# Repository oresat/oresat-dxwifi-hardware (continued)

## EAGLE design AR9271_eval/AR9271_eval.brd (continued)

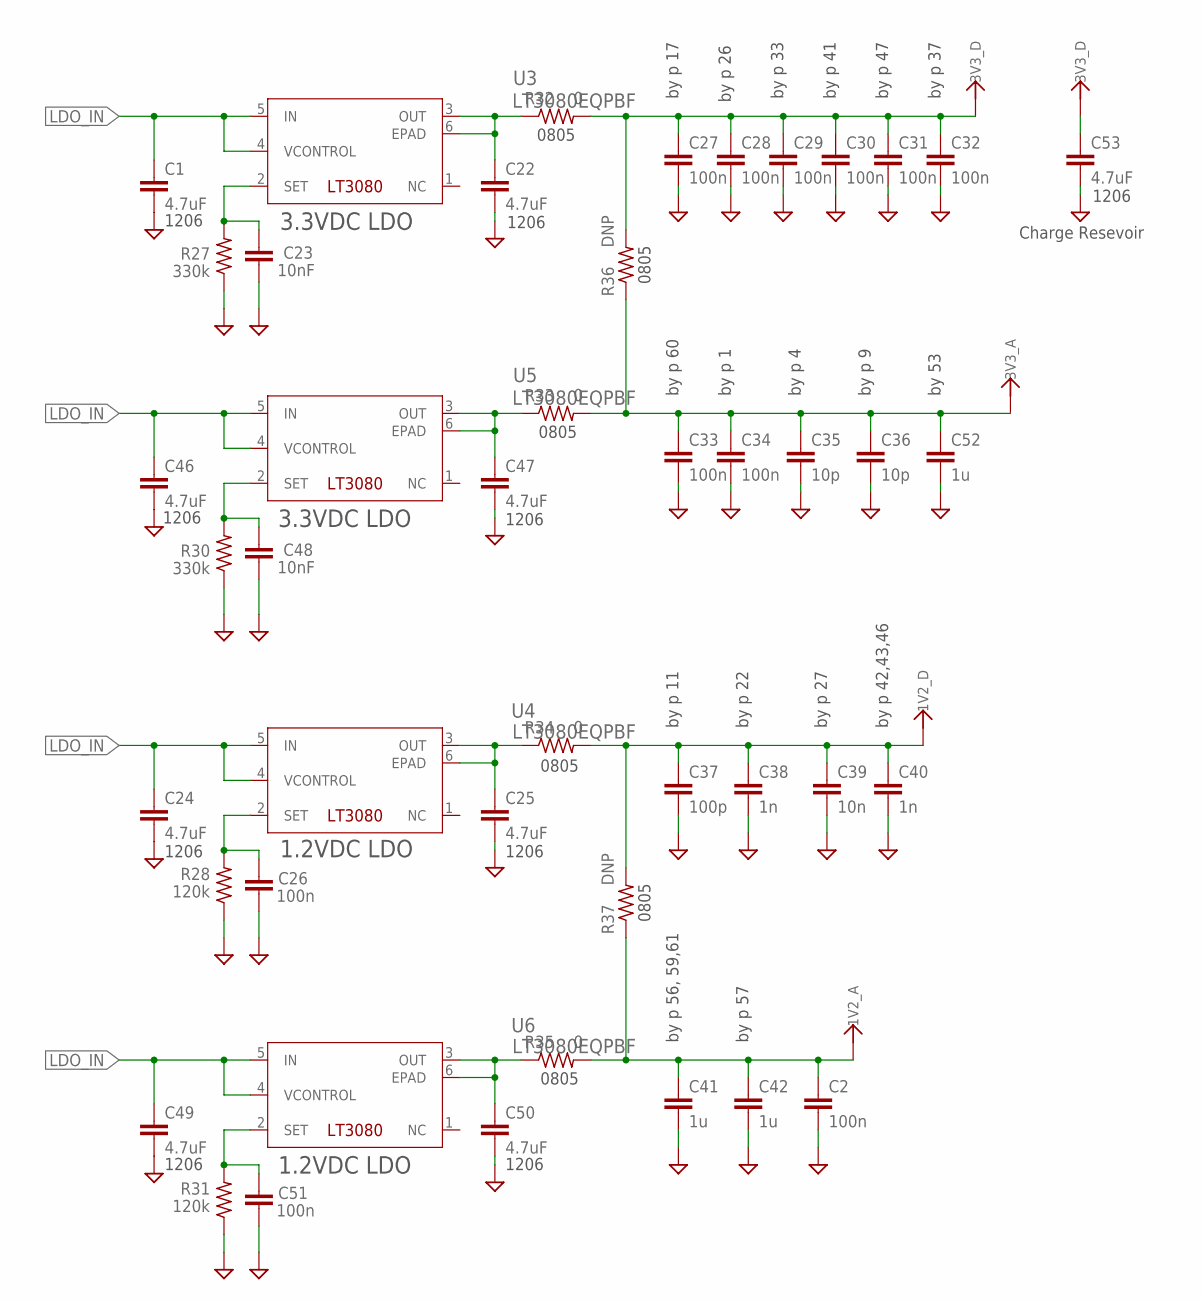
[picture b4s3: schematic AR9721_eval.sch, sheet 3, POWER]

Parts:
C1, C22, C24, C25, C46, C47, C49, C50, C53: 4.7uF; C1206; MPN GCM31CR71C475KA37L
C2: 100n; .0402-B-NOSILK; MPN GRM155R70J105KA12J
C23, C48: 10nF; .0402-B-NOSILK; MPN C0402C103K4RACAUTO
C26, C27, C28, C29, C30, C31, C32, C33, C34, C51: 100n; .0402-B-NOSILK; MPN CGA2B1X7R1C104K050BC
C35, C36: 10p; .0402-B-NOSILK; MPN CGA2B2C0G1H100D050BA
C37: 100p; .0402-B-NOSILK; MPN CGA2B2C0G1H101J050BA
C38, C40: 1n; .0402-B-NOSILK; MPN C0402C102K5GACTU
C39: 10n; .0402-B-NOSILK; MPN C0402C103K4RACAUTO
C41, C42: 1u; .0402-B-NOSILK; MPN GRM155R70J105KA12J
C52: 1u; .0402-B-NOSILK; MPN CGA2B2C0G1H100D050BA
R27, R30: 330k; .0402-A-NOSILK; MPN ERJ-2RKF3303X
R28, R31: 120k; .0402-A-NOSILK; MPN ERJ-2RKF1203X
R32, R33, R34, R35: 0; .0805-B; MPN ERJ-6GEY0R00V
R36, R37: DNP; .0805-B; MPN ERJ-6GEY0R00V
U3, U4, U5, U6: LT3080EQPBF; DDPAK-5_Q

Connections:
1V2_A: C2.1, C41.1, C42.1, R35.2, R37.1; also elsewhere on the board
1V2_D: C37.1, C38.1, C39.1, C40.1, R34.2, R37.2; also elsewhere on the board
3V3_A: C33.1, C34.1, C35.1, C36.1, C52.1, R33.2, R36.1; also elsewhere on the board
3V3_D: C27.1, C28.1, C29.1, C30.1, C31.1, C32.1, C53.1, R32.2, R36.2; also elsewhere on the board
GND: C1.2, C2.2, C22.2, C23.2, C24.2, C25.2, C26.2, C27.2, C28.2, C29.2, C30.2, C31.2, C32.2, C33.2, C34.2, C35.2, C36.2, C37.2, C38.2, C39.2, C40.2, C41.2, C42.2, C46.2, C47.2, C48.2, C49.2, C50.2, C51.2, C52.2, C53.2, R27.1, R28.1, R30.1, R31.1; also elsewhere on the board
LDO_IN: C1.1, C24.1, C46.1, C49.1, U3.4 (VCONTROL), U3.5 (IN), U4.4 (VCONTROL), U4.5 (IN), U5.4 (VCONTROL), U5.5 (IN), U6.4 (VCONTROL), U6.5 (IN); also elsewhere on the board
unnamed: C23.1, R27.2, U3.2 (SET)
unnamed: C26.1, R28.2, U4.2 (SET)
unnamed: C22.1, R32.1, U3.3 (OUT), U3.6 (EPAD)
unnamed: C25.1, R34.1, U4.3 (OUT), U4.6 (EPAD)
unnamed: C48.1, R30.2, U5.2 (SET)
unnamed: C47.1, R33.1, U5.3 (OUT), U5.6 (EPAD)
unnamed: C51.1, R31.2, U6.2 (SET)
unnamed: C50.1, R35.1, U6.3 (OUT), U6.6 (EPAD)

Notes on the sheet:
0805
3.3VDC LDO
1.2VDC LDO
1206
by p 60
by p 1
by p 4
by p 9
by p 17
by p 26
by p 33
by p 41
by p 47
by p 37
by p 11
by p 22
by p 27
by p 42,43,46
by p 56, 59,61
by p 57
by 53
Charge Resevoir

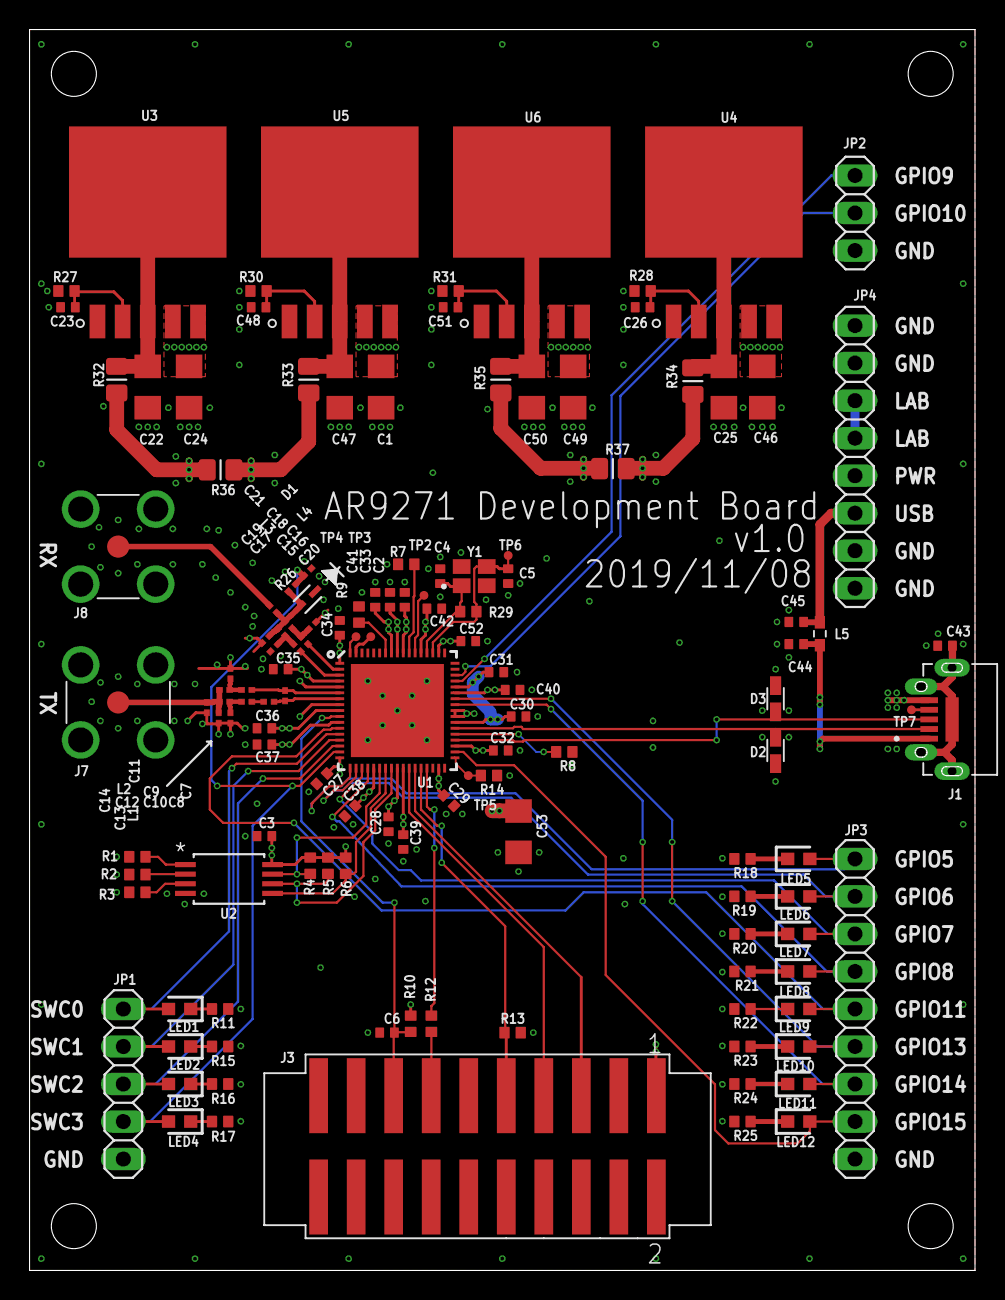
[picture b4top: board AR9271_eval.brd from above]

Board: 4 copper layers, 64.0 x 84.0 mm, 135 parts (0 on the bottom side), 80 nets.

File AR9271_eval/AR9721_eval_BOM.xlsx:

Bill Of Materials for AR9721
Source file: AR9721_eval.sch
Last modified: 2019/09/17
PCB version: 1.0 |  |  | P/DNP = | Place/Do Not Place (DNP is for final production boards)
BOM revision: 0 |  |  | Generic = | Any generic part with the same characteristics are OK (e.g., bypass cap)
Cnt | Part References | P/DNP | Mfg | Mfg PN | Description | Generic | Dist | Dist Part Number
9 | C1, C22, C24, C25, C46, C47, C49, C50, C53 | P | Murata Electronics | GCM31CR71C475KA37L | Capacitor, 4.7uF, 1206 | Y | Digi-key | 490-6065-1-ND
4 | C10, C11, C12, C13 | P | Taiyo Yuden | UMK063CG020CTHF | Capacitor, 2pF, 0201 | Y | Digi-key | 587-3777-2-ND
2 | C14, C19 | P | Taiyo Yuden | UMK063CG010CTHF | Capacitor, 1pF, 0201 | Y | Digi-key | 587-3776-1-ND
2 | C17, C18 | P | Taiyo Yuden | UMK063CG1R5CT-F | Capacitor, 1.5pF, 0201 | Y | Digi-key | 587-3202-6-ND
15 | C2, C3, C6, C26, C27, C28, C29, C30, C31, C32, C33, C34, C43, C45, C51 | P | TDK | CGA2B1X7R1C104K050BC | Capacitor, 100nF, 0402 | Y | Digi-key | 445-5613-1-ND
1 | C21 | P | Taiyo Yuden | UMK063CG101JT-F | Capacitor, 100pF, 0201 | Y | Digi-key | 587-3207-2-ND
4 | C23, C39, C44, C48 | P | Kemet | C0402C103K4RACAUTO | Capacitor, 10nF, 0402 | Y | Digi-key | 399-6825-1-ND
1 | C37 | P | TDK | CGA2B2C0G1H101J050BA | Capacitor, 100pF, 0402 | Y | Digi-key | 445-5596-1-ND
2 | C38, C40 | P | Kemet | C0402C102K5GACTU | Capacitor, 1nF, 0402 | Y | Digi-key | 399-7756-1-ND
4 | C4, C5, C35, C36 | P | Yageo | CC0402JRNPO9BN100 | Capacitor, 10pF, 0402 | Y | Digi-key | 311-1014-1-ND
3 | C41, C42, C52 | P | TDK | CGA2B2C0G1H100D050BA | Capacitor, 1uF, 0402 | Y | Digi-key | 445-5584-1-ND
1 | C7 | P | Taiyo Yuden | UMK063CG2R2CTHF | Capacitor, 2.2pF, 0201 | Y | Digi-key | 587-5314-1-ND
5 | C8, C9, C15, C16, C20 | P | Taiyo Yuden | UMK063CG100DTHF | Capacitor, 10pF, 0201 | Y | Digi-key | 587-3785-2-ND
1 | D1 | P | Skyworks | SMP1321-079 | RF PIN Diode | N | Digi-key | 863-1099-1-ND
2 | D2, D3 | P | Littelfuse Inc. | PGB1010603MR | PGB1 Series 15 V 63 Bi-Directional SMT ESD TVS | Y | Digi-key | F2594CT-ND
1 | J1 | P | CUI Inc. | UJ2-MIBH2-4-SMT-TR | Micro B Type 5 Pin Horizontal SMT USB Jack 2.0 | Y | Digi-key | 102-4007-1-ND
1 | J3 | P | Samtec Inc. | HTST-110-01-L-DV-P | Conn Shrouded Header HDR 20 POS 2.54mm Solder ST SMD | Y | Digi-key | SAM15675-ND
2 | J7, J8 | P | Amphenol RF | 132134-15 | Rf Coaxial, Sma, Straight Jack, Pcb | Y | Digi-key | ACX1962-ND
4 | JP1, JP2, JP3, JP4 | P | NA | NA | PIN HEADER | Y | Digi-key | 952-3308-ND
2 | L1, L2 | P | Murata Electronics | LQP03TN1N8B02D | Inductor, 1.8nH, 0201 | Y | Digi-key | 490-6720-1-ND
2 | L3, L4 | P | Murata Electronics | LQP03TN2N2B02D | Inductor, 2.2nH, 0201 | Y | Digi-key | 490-6723-1-ND
1 | L5 | P | Murata Electronics | BLM18PG221SH1D | FERRITE BEAD 220 OHM 0603 1LN | N | Digi-key | 490-7817-1-ND
12 | LED1, LED2, LED3, LED4, LED5, LED6, LED7, LED8, LED9, LED10, LED11, LED12 | P | Lite-On | LTST-C193KGKT-5A | LED,Green,0603, | Y | Digi-key | 160-1828-1-ND
3 | R1, R36, R37 | NP | NA | NA | NA | NA | NA | NA
12 | R11, R15, R16, R17, R18, R19, R20, R21, R22, R23, R24, R25 | P | Panasonic | ERJ-2GEJ511X | Resistor, 510, 0402 | Y | Digi-key | P510JTR-ND
1 | R12 | P | Panasonic | ERJ-2GEJ330X | Resistor, 33, 0402 | Y | Digi-key | P33JCT-ND
2 | R2, R3 | P | Panasonic | ERJ-2GE0R00X | Resistor, 0, 0402 | Y | Digi-key | P0.0JCT-ND
1 | R26 | P | Panasonic | ERJ-1GNF1001C | Resistor, 1k, 0201 | Y | Digi-key | P122413CT-ND
2 | R27, R30 | P | Panasonic | ERJ-2RKF3303X | Resistor, 330k, 0402 | Y | Digi-key | P330KLCT-ND
2 | R28, R31 | P | Panasonic | ERJ-2RKF1203X | Resistor, 120k, 0402 | Y | Digi-key | P120KLCT-ND
1 | R29 | P | Panasonic | ERJ-2GEJ105X | Resistor, 1M, 0402 | Y | Digi-key | P1.0MJTR-ND
4 | R32, R33, R34, R35 | P | Panasonic | ERJ-6GEY0R00V | Resistor, 0, 0805 | Y | Digi-key | P0.0ACT-ND
5 | R4, R7, R10, R13, R14 | P | Panasonic | ERJ-2GEJ103X | Resistor, 10k, 0402 | Y | Digi-key | ERJ-2GEJ103X
2 | R5, R6 | P | Panasonic | ERJ-2GEJ103X | Resistor, 4.7k, 0402 | Y | Digi-key | P10KJCT-ND
1 | R8 | P | Panasonic | ERJ-2RKF51R1X | Resistor, 51.1, 0402 | Y | Digi-key | P51.1LCT-ND
1 | R9 | P | Panasonic | ERJ-2RKF6191X | Resistor, 6.19k, 0402 | Y | Digi-key | P6.19KLCT-ND
1 | U1 | P | Atheros | AR9271-AL1A | Atheros WiFi WLAN IC | N | AliExpress | N/A
1 | U2 | P | Microchip | AT24C04CXHMT | EEPROM with I2C interface | N | Digi-key | AT24C04C-XHM-TCT-ND
4 | U3, U4, U5, U6 | P | Analog Devices | LT3080EQ#PBF | Adj. 1.1A Single Res LDO Regulator | N | Digi-key | LT3080EQ#PBF-ND
1 | Y1 | P | ECS International | ECS-400-10-36-CKY-TR | Crystal 40mhz 10pf Smd | N | Digi-key | XC2666CT-ND
VERSION INFO
Rev | Date | Notes
1 | 43725 | First rev BOM

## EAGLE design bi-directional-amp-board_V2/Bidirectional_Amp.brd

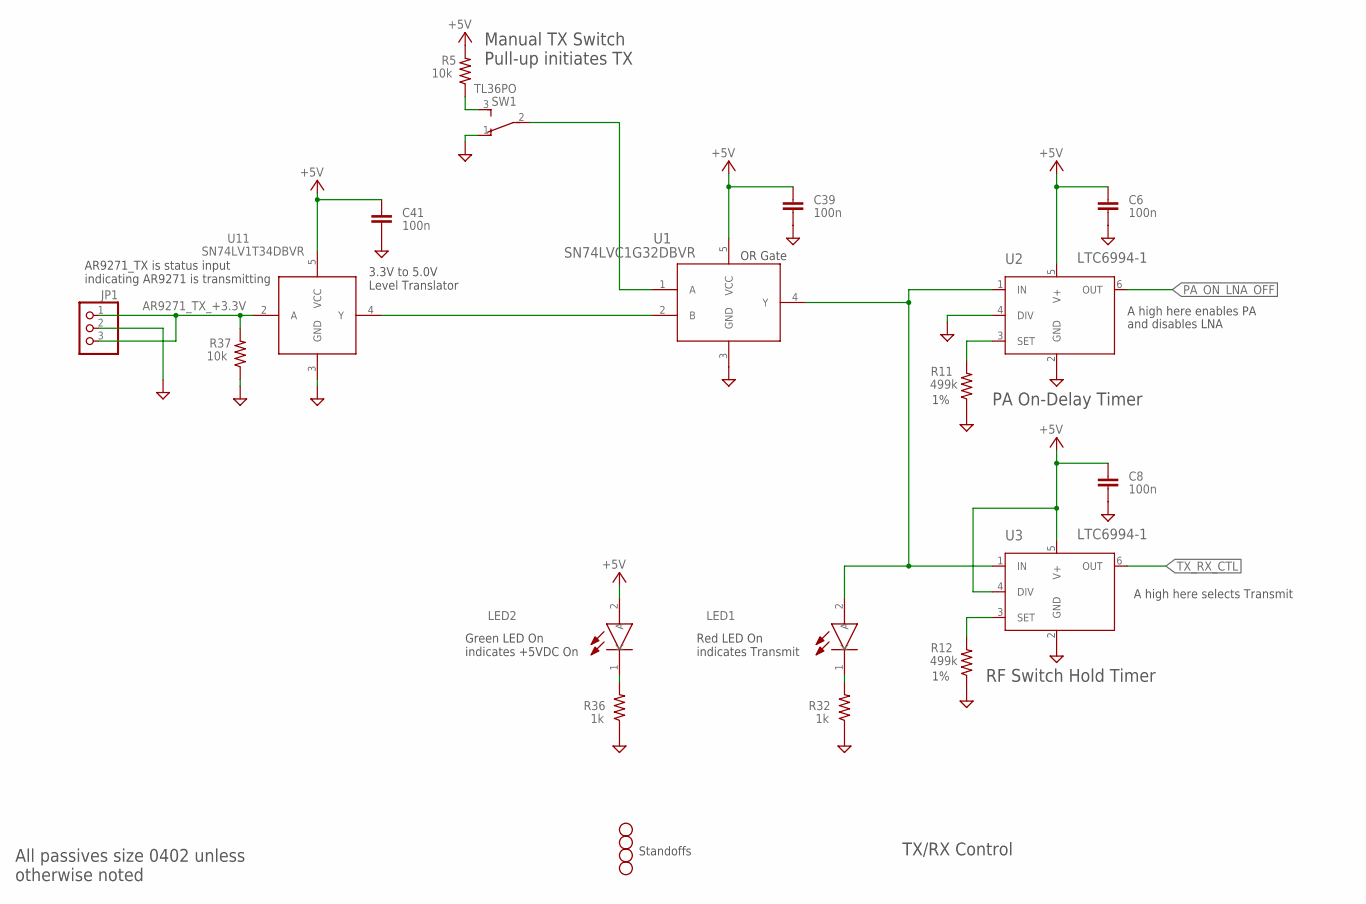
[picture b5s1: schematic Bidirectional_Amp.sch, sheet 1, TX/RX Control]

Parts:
C6, C8, C39, C41: 100n; .0402-B-NOSILK; MPN CGA2B1X7R1C104K050BC
H1, H2, H3, H4: STAND-OFFTIGHT; STAND-OFF-TIGHT
JP1: PINHD-1X3; 1X03; MPN 22-23-2031
LED1: LTST-C193KRKT-5A; LEDC1607X80N
LED2: LTST-C193KGKT-5A; LEDC1607X80N
R5, R37: 10k; .0402-B-NOSILK; MPN ERJ-2GEJ103X
R11, R12: 499k; .0402-B-NOSILK; MPN ERJ-2RKF4993X
R32, R36: 1k; .0402-B-NOSILK; MPN ERJ-2GEJ102X
SW1: TL36PO; TL3XPO; MPN TL36P005000
U1: SN74LVC1G32DBVR; DBV5
U2, U3: LTC6994-1; TSOT-23_S6
U11: SN74LV1T34DBVR; SOT95P280X145-5N

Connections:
+5V: C6.1, C8.1, C39.1, C41.1, LED2.2 (A), R5.2, U1.5 (VCC), U2.5 (V+), U3.4 (DIV), U3.5 (V+), U11.5 (VCC); also elsewhere on the board
AR9271_TX_+3.3V: JP1.1, JP1.3, R37.2, U11.2 (A)
GND: C6.2, C8.2, C39.2, C41.2, JP1.2, R11.1, R12.1, R32.1, R36.1, R37.1, SW1.1 (O), U1.3 (GND), U2.2 (GND), U2.4 (DIV), U3.2 (GND), U11.3 (GND); also elsewhere on the board
unnamed: R5.1, SW1.3 (S)
unnamed: SW1.2, U1.1 (A)
unnamed: LED1.2 (A), U1.4 (Y), U2.1 (IN), U3.1 (IN)
unnamed: R11.2, U2.3 (SET)
unnamed: U1.2 (B), U11.4 (Y)
unnamed: R12.2, U3.3 (SET)
unnamed: LED1.1 (K), R32.2
unnamed: LED2.1 (K), R36.2
PA_ON_LNA_OFF: U2.6 (OUT); also elsewhere on the board
TX_RX_CTL: U3.6 (OUT); also elsewhere on the board

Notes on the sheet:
PA On-Delay Timer
RF Switch Hold Timer
Manual TX Switch Pull-up initiates TX
A high here enables PA
and disables LNA
A high here selects Transmit
AR9271_TX is status input indicating AR9271 is transmitting
TX/RX Control
Red LED On indicates Transmit
Green LED On indicates +5VDC On
OR Gate
3.3V to 5.0V Level Translator
Standoffs
All passives size 0402 unless otherwise noted

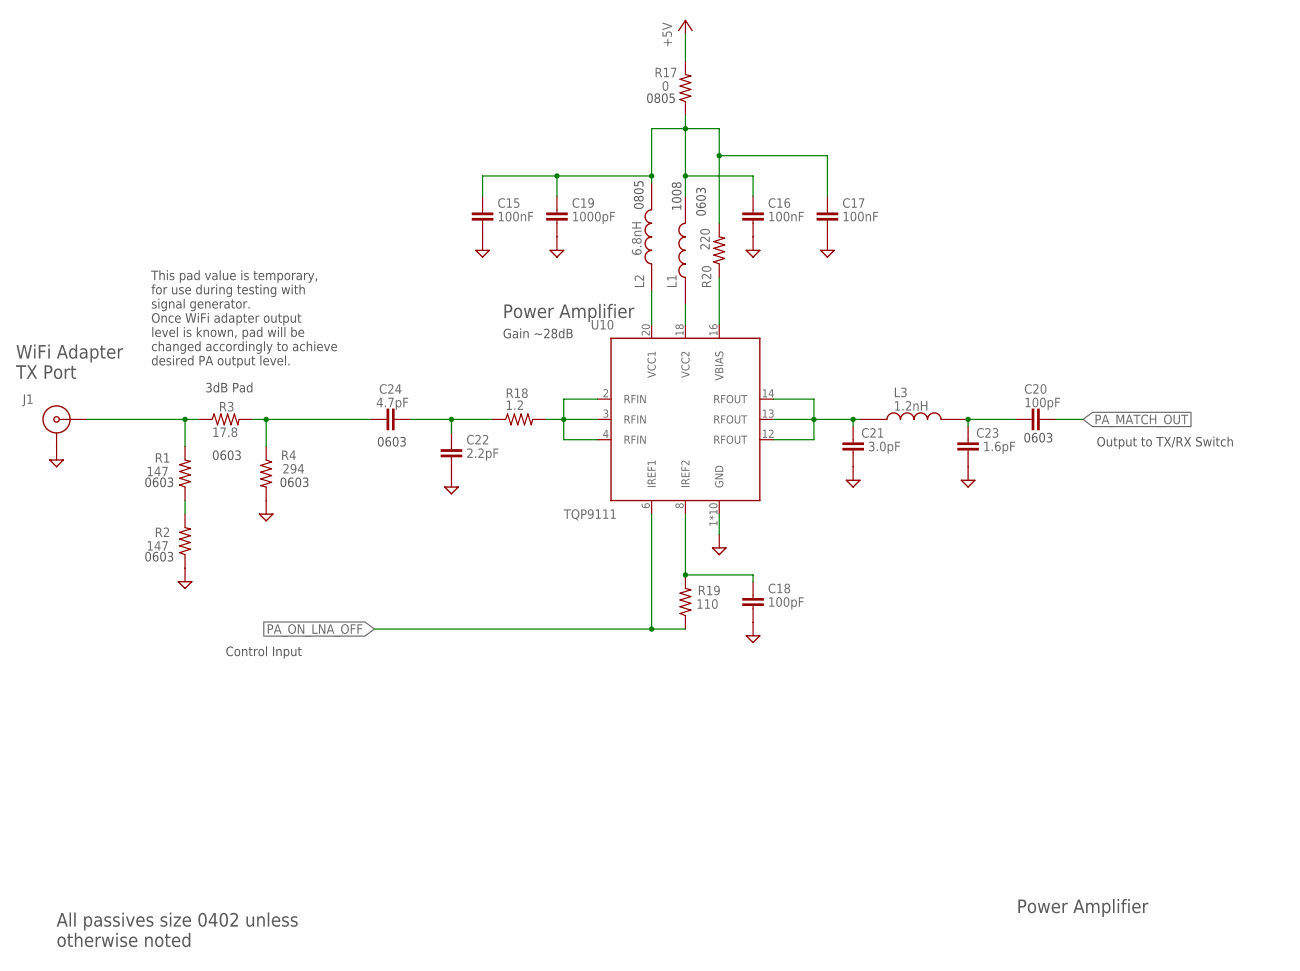
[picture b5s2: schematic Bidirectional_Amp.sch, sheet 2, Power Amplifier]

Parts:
C15, C16, C17: 100nF; .0402-B-NOSILK; MPN CGA2B1X7R1C104K050BC
C18: 100pF; .0402-B-NOSILK; MPN GCM1555C1H101JA16D
C19: 1000pF; .0402-B-NOSILK; MPN CGA2B2NP01H102J050BA
C20: 100pF; .0603-C-NOSILK; MPN GCM1885C1H101JA16D
C21: 3.0pF; .0402-C-NOSILK; MPN UVK105CG030JW-F
C22: 2.2pF; .0402-C-NOSILK; MPN UVK105CG2R2JW-F
C23: 1.6pF; .0402-C-NOSILK; MPN GJM1555C1H1R6BB01D
C24: 4.7pF; .0603-C-NOSILK; MPN 06032U4R7BAT2A
J1: 142-0701-851_ALT; 142-0701-851; MPN 142-0701-851
L1: 1008HQ-10NXJLB1008_IMPERIAL_2520_METRIC; INDC2520X120N; MPN 1008HQ-10NXJLB
L2: 6.8nH; 0805CS
L3: 1.2nH; 0402CS1N2XJLW
R1, R2: 147; .0603-C-NOSILK; MPN ERJ-3EKF1470V
R3: 17.8; .0603-C-NOSILK; MPN ERJ-3EKF17R8V
R4: 294; .0603-C-NOSILK; MPN ERJ-3EKF2940V
R17: 0; R0805; MPN ERJ-6GEY0R00V
R18: 1.2; R0402; MPN ERJ-2GEJ1R2X
R19: 110; .0402-B-NOSILK; MPN ERJ-2RKF1100X
R20: 220; .0603-C-NOSILK; MPN ERJ-3EKF2200V
U10: TQP9111; QFN50P400X400X102-21N

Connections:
+5V: R17.2; also elsewhere on the board
GND: C15.2, C16.2, C17.2, C18.2, C19.2, C21.2, C22.2, C23.2, J1.GND1 (GND), J1.GND2 (GND), J1.GND3 (GND), J1.GND4 (GND), R2.1, R4.2, U10.1 (GND), U10.5 (GND), U10.7 (GND), U10.9 (GND), U10.10 (GND), U10.11 (GND), U10.15 (GND), U10.17 (GND), U10.19 (GND), U10.21 (GND); also elsewhere on the board
unnamed: J1.RF1 (CTR), R1.2, R3.1
unnamed: R1.1, R2.2
unnamed: L1.1, U10.18 (VCC2)
unnamed: C15.1, C16.1, C17.1, C19.1, L1.2, L2.2, R17.1, R20.2
unnamed: C18.1, R19.2, U10.8 (IREF2)
unnamed: C21.1, L3.1, U10.12 (RFOUT), U10.13 (RFOUT), U10.14 (RFOUT)
unnamed: C22.1, C24.2, R18.1
unnamed: C20.1, C23.1, L3.2
unnamed: R20.1, U10.16 (VBIAS)
unnamed: L2.1, U10.20 (VCC1)
unnamed: R18.2, U10.2 (RFIN), U10.3 (RFIN), U10.4 (RFIN)
PA_MATCH_OUT: C20.2; also elsewhere on the board
PA_ON_LNA_OFF: R19.1, U10.6 (IREF1); also elsewhere on the board
PA_PAD_OUT: C24.1, R3.2, R4.1

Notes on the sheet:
0603
1008
0805
Power Amplifier
Output to TX/RX Switch
Control Input
Gain ~28dB
3dB Pad
This pad value is temporary, for use during testing with signal generator. Once WiFi adapter output level is known, pad will be changed accordingly to achieve desired PA output level.
WiFi Adapter TX Port
All passives size 0402 unless otherwise noted

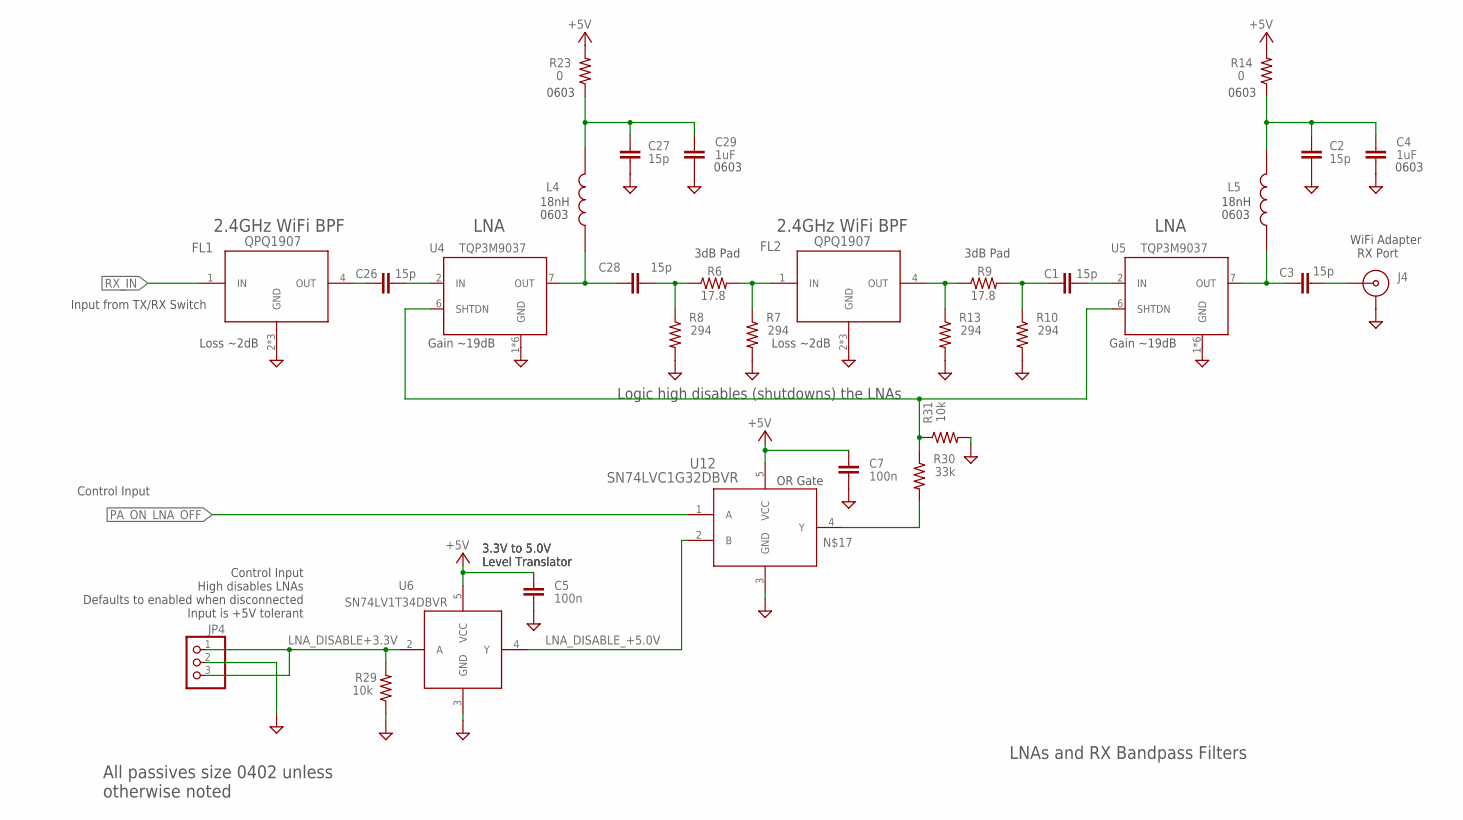
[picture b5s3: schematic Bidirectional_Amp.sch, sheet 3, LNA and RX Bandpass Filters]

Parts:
C1, C3, C26, C28: 15p; .0402-C-NOSILK; MPN GJM1555C1H150JB01D
C2, C27: 15p; .0402-B-NOSILK; MPN GJM1555C1H150JB01D
C4, C29: 1uF; .0603-B-NOSILK; MPN C0603X105M4RACAUTO
C5, C7: 100n; .0402-B-NOSILK; MPN CGA2B1X7R1C104K050BC
FL1, FL2: QPQ1907; FIL_B39162B9417K610; MPN QPQ1907
J4: 142-0701-851_ALT; 142-0701-851; MPN 142-0701-851
JP4: PINHD-1X3; 1X03; MPN 22-23-2031
L4, L5: 68nH; 0603CS-68NXJLW; MPN 0603CS-18NXJLW
R6, R9: 17.8; .0402-C-NOSILK; MPN ERJ-2RKF17R8X
R7, R8, R10, R13: 294; .0402-C-NOSILK; MPN ERJ-2RKF2940X
R14, R23: 0; .0603-B-NOSILK; MPN ERJ-3GEY0R00V
R29: 10k; .0402-B-NOSILK; MPN ERJ-2GEJ103X
R30: 33k; .0402-B-NOSILK; MPN ERJ-2RKF2940X
R31: 10k; .0402-B-NOSILK; MPN ERJ-2RKF2940X
U4, U5: TQP3M9037; DFN8-2X2-WITH-PAD; MPN TQP3M9037
U6: SN74LV1T34DBVR; SOT95P280X145-5N
U12: SN74LVC1G32DBVR; DBV5

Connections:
+5V: C5.1, C7.1, R14.2, R23.2, U6.5 (VCC), U12.5 (VCC); also elsewhere on the board
GND: C2.1, C4.2, C5.2, C7.2, C27.1, C29.2, FL1.2 (GND), FL1.3 (GND), FL1.5 (GND), FL2.2 (GND), FL2.3 (GND), FL2.5 (GND), J4.GND1 (GND), J4.GND2 (GND), J4.GND3 (GND), J4.GND4 (GND), JP4.2, R7.2, R8.2, R10.2, R13.2, R29.1, R31.2, U4.1 (GND), U4.3 (GND), U4.4 (GND), U4.5 (GND), U4.8 (GND), U4.PAD (GND), U5.1 (GND), U5.3 (GND), U5.4 (GND), U5.5 (GND), U5.8 (GND), U5.PAD (GND), U6.3 (GND), U12.3 (GND); also elsewhere on the board
LNA_DISABLE+3.3V: JP4.1, JP4.3, R29.2, U6.2 (A)
LNA_DISABLE_+5.0V: U6.4 (Y), U12.2 (B)
LNA_ON_OFF: R30.1, R31.1, U4.6 (SHTDN), U5.6 (SHTDN)
unnamed: C28.2, R6.1, R8.1
unnamed: FL2.4 (OUT), R9.1, R13.1
unnamed: C1.2, U5.2 (IN)
unnamed: C3.1, L5.1, U5.7 (OUT)
unnamed: C2.2, C4.1, L5.2, R14.1
unnamed: C3.2, J4.RF1 (CTR)
unnamed: R30.2, U12.4 (Y)
unnamed: C26.2, U4.2 (IN)
unnamed: C28.1, L4.1, U4.7 (OUT)
unnamed: C27.2, C29.1, L4.2, R23.1
unnamed: C26.1, FL1.4 (OUT)
PA_ON_LNA_OFF: U12.1 (A); also elsewhere on the board
PA_PAD_OUT1: FL2.1 (IN), R6.2, R7.1
PA_PAD_OUT2: C1.1, R9.2, R10.1
RX_IN: FL1.1 (IN); also elsewhere on the board

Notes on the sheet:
0603
LNA
2.4GHz WiFi BPF
LNAs and RX Bandpass Filters
Input from TX/RX Switch
Control Input
WiFi Adapter RX Port
Gain ~19dB
Loss ~2dB
18nH
3dB Pad
All passives size 0402 unless otherwise noted
Control Input High disables LNAs Defaults to enabled when disconnected Input is +5V tolerant
3.3V to 5.0V Level Translator
OR Gate
Logic high disables (shutdowns) the LNAs

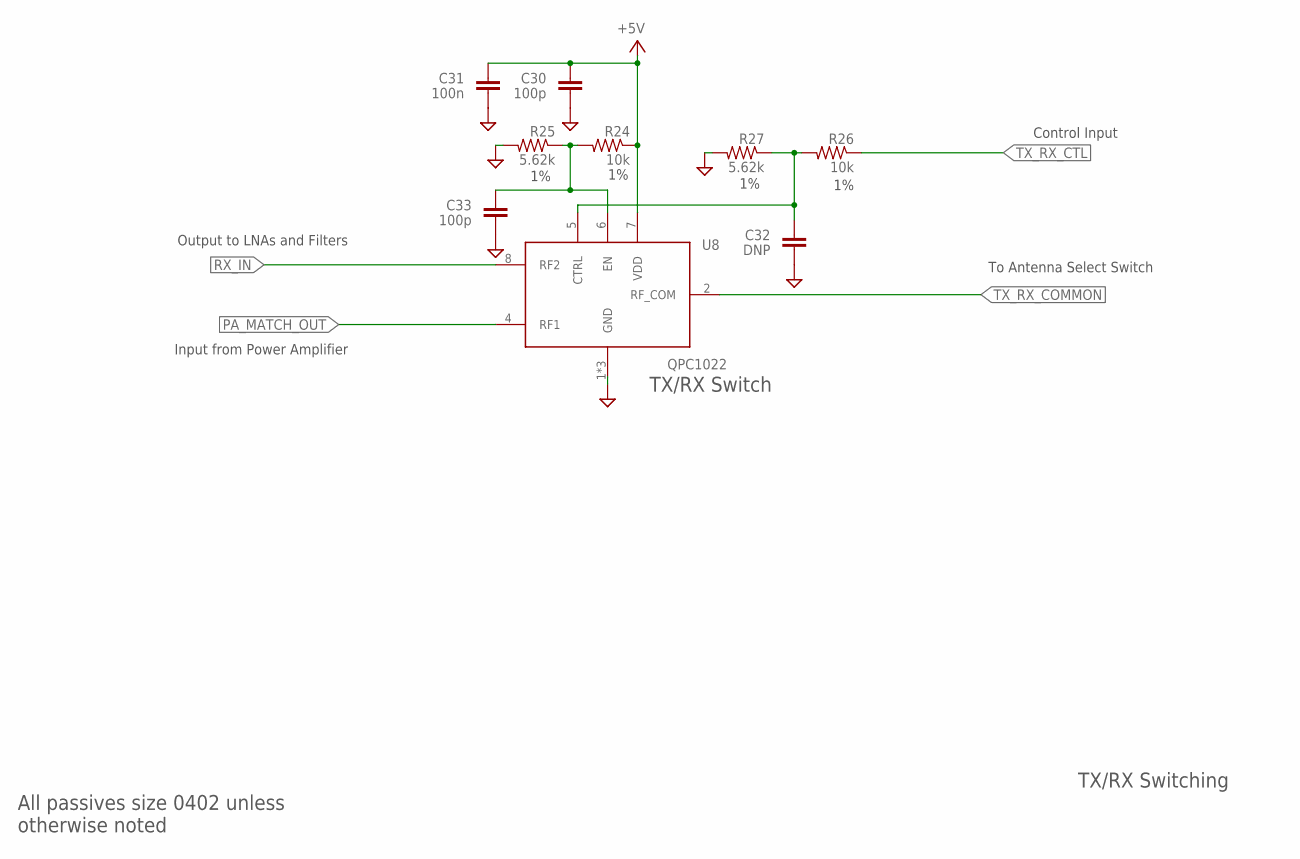
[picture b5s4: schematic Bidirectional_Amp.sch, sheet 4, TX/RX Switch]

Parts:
C30, C33: 100p; .0402-B-NOSILK; MPN GCM1555C1H101JA16D
C31: 100n; .0402-B-NOSILK; MPN CGA2B1X7R1C104K050BC
C32: DNP; .0402-B-NOSILK
R24, R26: 10k; .0402-B-NOSILK; MPN ERJ-2RKF1002X
R25, R27: 5.62k; .0402-B-NOSILK; MPN ERJ-2RKF5621X
U8: QPC1022

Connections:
+5V: C30.1, C31.1, R24.1, U8.7 (VDD); also elsewhere on the board
GND: C30.2, C31.2, C32.2, C33.2, R25.2, R27.2, U8.1 (GND), U8.3 (GND), U8.9 (GND); also elsewhere on the board
PA_MATCH_OUT: U8.4 (RF1); also elsewhere on the board
RX_IN: U8.8 (RF2); also elsewhere on the board
TXRX-CTRL: C32.1, R26.2, R27.1, U8.5 (CTRL)
TXRX-EN: C33.1, R24.2, R25.1, U8.6 (EN)
TX_RX_COMMON: U8.2 (RF_COM); also elsewhere on the board
TX_RX_CTL: R26.1; also elsewhere on the board

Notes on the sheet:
TX/RX Switch
TX/RX Switching
Input from Power Amplifier
Output to LNAs and Filters
Control Input
To Antenna Select Switch
All passives size 0402 unless otherwise noted

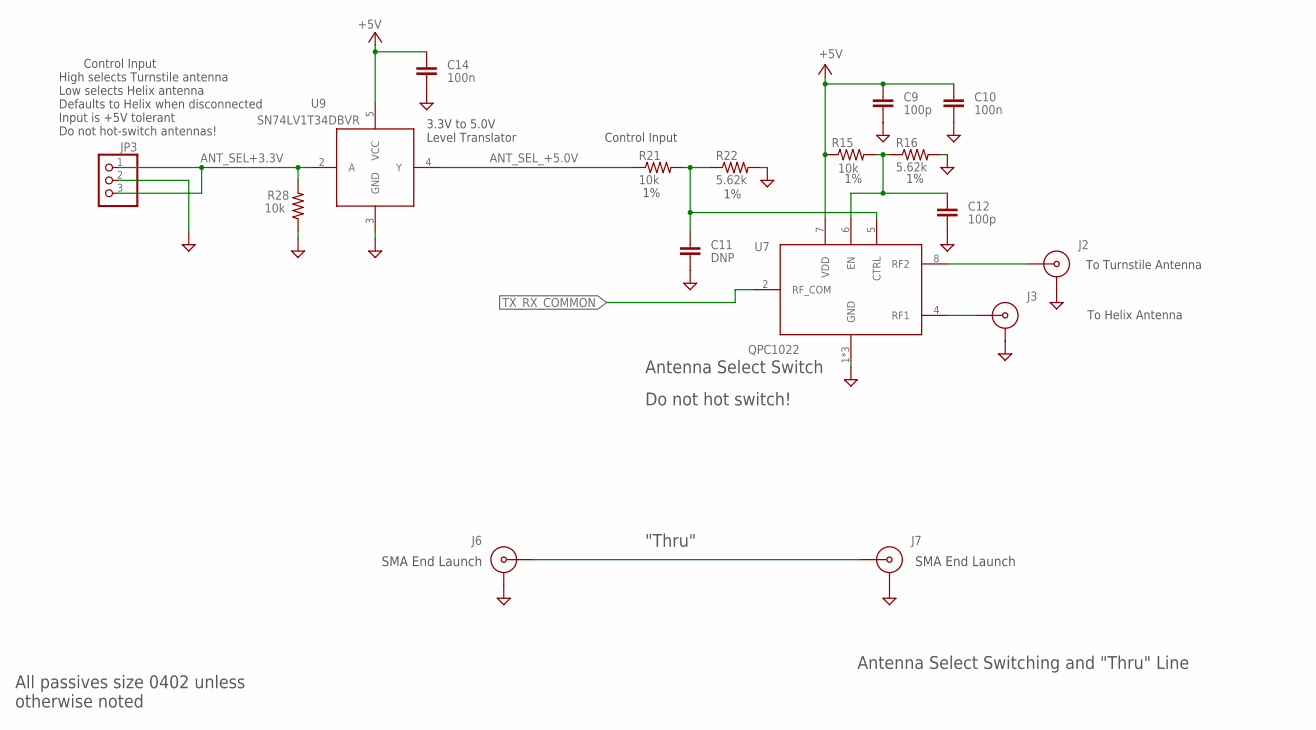
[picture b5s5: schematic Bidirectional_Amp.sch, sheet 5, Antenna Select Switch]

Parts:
C9, C12: 100p; .0402-B-NOSILK; MPN GCM1555C1H101JA16D
C10, C14: 100n; .0402-B-NOSILK; MPN CGA2B1X7R1C104K050BC
C11: DNP; .0402-B-NOSILK; MPN GCM1555C1H101JA16D
J2, J3, J6, J7: 142-0701-851_ALT; 142-0701-851; MPN 142-0701-851
JP3: PINHD-1X3; 1X03; MPN 22-23-2031
R15, R21: 10k; .0402-B-NOSILK; MPN ERJ-2RKF1002X
R16, R22: 5.62k; .0402-B-NOSILK; MPN ERJ-2RKF5621X
R28: 10k; .0402-B-NOSILK; MPN ERJ-2GEJ103X
U7: QPC1022
U9: SN74LV1T34DBVR; SOT95P280X145-5N

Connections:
+5V: C9.1, C10.1, C14.1, R15.1, U7.7 (VDD), U9.5 (VCC); also elsewhere on the board
ANT_SEL+3.3V: JP3.1, JP3.3, R28.2, U9.2 (A)
ANT_SEL_+5.0V: R21.1, U9.4 (Y)
AS-CTRL: C11.1, R21.2, R22.1, U7.5 (CTRL)
AS-EN: C12.1, R15.2, R16.1, U7.6 (EN)
GND: C9.2, C10.2, C11.2, C12.2, C14.2, J2.GND1 (GND), J2.GND2 (GND), J2.GND3 (GND), J2.GND4 (GND), J3.GND1 (GND), J3.GND2 (GND), J3.GND3 (GND), J3.GND4 (GND), J6.GND1 (GND), J6.GND2 (GND), J6.GND3 (GND), J6.GND4 (GND), J7.GND1 (GND), J7.GND2 (GND), J7.GND3 (GND), J7.GND4 (GND), JP3.2, R16.2, R22.2, R28.1, U7.1 (GND), U7.3 (GND), U7.9 (GND), U9.3 (GND); also elsewhere on the board
HELICAL: J2.RF1 (CTR), U7.8 (RF2)
THROUGH: J6.RF1 (CTR), J7.RF1 (CTR)
TURNSTILE: J3.RF1 (CTR), U7.4 (RF1)
TX_RX_COMMON: U7.2 (RF_COM); also elsewhere on the board

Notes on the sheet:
Antenna Select Switching and "Thru" Line
"Thru"
SMA End Launch
Antenna Select Switch
To Helix Antenna
To Turnstile Antenna
Control Input
Control Input High selects Turnstile antenna Low selects Helix antenna Defaults to Helix when disconnected Input is +5V tolerant Do not hot-switch antennas!
3.3V to 5.0V Level Translator
All passives size 0402 unless otherwise noted
Do not hot switch!

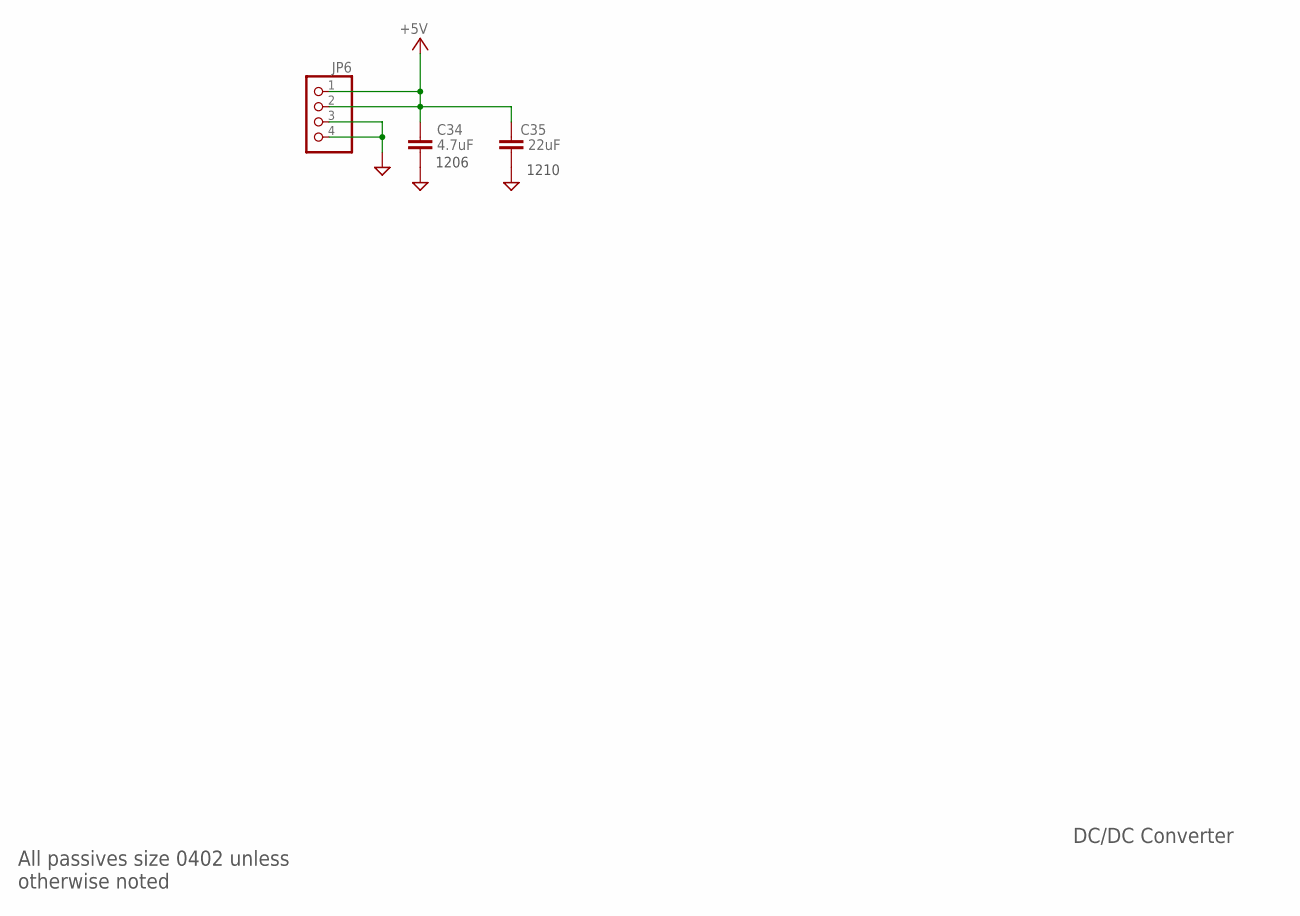
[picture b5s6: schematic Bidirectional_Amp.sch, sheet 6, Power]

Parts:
C34: 4.7uF; C1206; VOLTAGE 16V; MPN GCJ31CR71C475KA01L
C35: 22uF; C1210; MPN GCJ32ER71C226KE01L
JP6: PINHD-1X4; 1X04

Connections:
+5V: C34.1, C35.1, JP6.1, JP6.2; also elsewhere on the board
GND: C34.2, C35.2, JP6.3, JP6.4; also elsewhere on the board

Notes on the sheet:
DC/DC Converter
1206
1210
All passives size 0402 unless otherwise noted

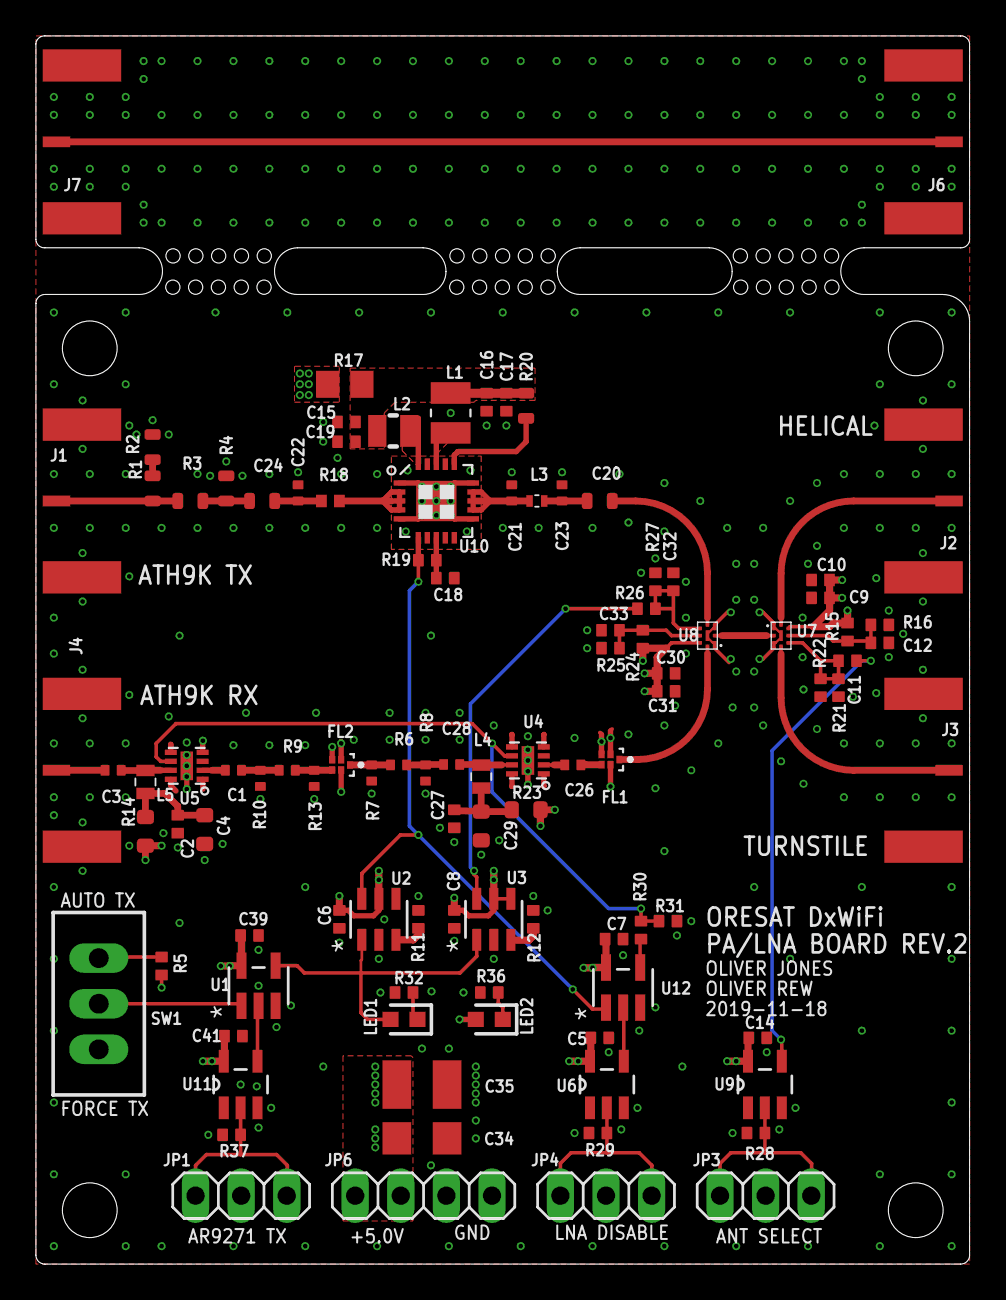
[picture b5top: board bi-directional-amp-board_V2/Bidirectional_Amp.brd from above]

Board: 4 copper layers, 52.0 x 68.4 mm, 105 parts (0 on the bottom side), 53 nets.
